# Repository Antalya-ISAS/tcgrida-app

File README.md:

# Antalya ISAS

## tcGrida's app codes. 

### What is tcGrida?
tcGrida is an explorer ROV that is capable of long duration and long-distance dives, autonomous emergency easy-surface*, live video feed, 4K@60 video recording, high-pressure durable and waterproof design with a wired, trustable and stable connection.

*: A solution that prevents your vehicle from getting lost in the water when the connection is lost, and makes it get back to the surface autonomously.

### Compatible Operating Systems:

-  &emsp; Windows 7 or newer

-  &emsp; macOS 10.6 or newer

-  &emsp; Most linux distros can run this app

## Our Social Media Accounts, Website and Discord Server

 Instagram: https://instagram.com/antalya.isas

 LinkedIn: https://linkedin.com/company/antalya-isas

 YouTube: https://cutt.ly/antalya-isas

 Website: https://antalyaisas.com

 Discord Server: https://discord.gg/peCKe2drMV

## Contact

E-mail: info@antalyaisas.com

Contact Form: https://antalyaisas.com/iletisim.html

Address: [Molla Yusuf Mah. Hürriyet Cad. No: 25 Konyaaltı/Antalya, Türkiye](https://goo.gl/maps/5YjF16fynHth8VVB9)

## Support Us!

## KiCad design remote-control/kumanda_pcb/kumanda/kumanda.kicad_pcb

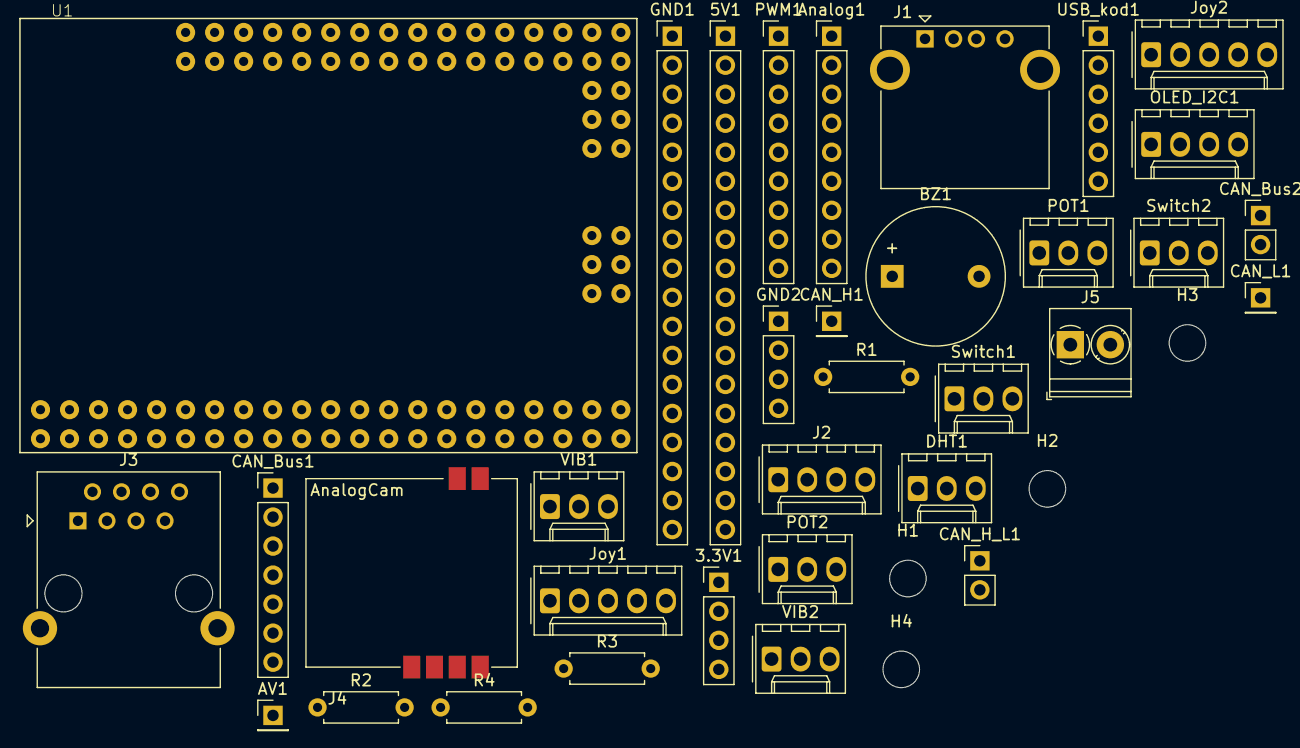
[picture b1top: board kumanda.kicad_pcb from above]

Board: 2 copper layers, 38 parts (0 on the bottom side), 51 nets, no tracks yet.

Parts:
3.3V1: Conn_01x04; PinHeader_1x04_P2.54mm_Vertical
5V1: Conn_01x18; PinHeader_1x18_P2.54mm_Vertical
AV1: Conn_01x01; PinHeader_1x01_P2.54mm_Vertical
Analog1: Conn_01x09; PinHeader_1x09_P2.54mm_Vertical
BZ1: Buzzer; Buzzer_12x9.5RM7.6
CAN_Bus1: Conn_01x07; PinHeader_1x07_P2.54mm_Vertical
CAN_Bus2: Conn_01x02; PinHeader_1x02_P2.54mm_Vertical
CAN_H1: Conn_01x01; PinHeader_1x01_P2.54mm_Vertical
CAN_H_L1: Conn_01x02; PinHeader_1x02_P2.54mm_Vertical
CAN_L1: Conn_01x01; PinHeader_1x01_P2.54mm_Vertical
DHT1: Conn_01x03; Molex_KK-254_AE-6410-03A_1x03_P2.54mm_Vertical
GND1: Conn_01x18; PinHeader_1x18_P2.54mm_Vertical
GND2: Conn_01x04; PinHeader_1x04_P2.54mm_Vertical
H1, H2, H3, H4: MountingHole; MountingHole_3.2mm_M3
J1: USB_A; USB_A_CONNFLY_DS1095-WNR0
J2: Conn_01x04; Molex_KK-254_AE-6410-04A_1x04_P2.54mm_Vertical
J3: RJ45; RJ45_Ninigi_GE
J4: Conn_01x06; Analog-cam
J5: Screw_Terminal_01x02; TerminalBlock_Phoenix_PT-1,5-2-3.5-H_1x02_P3.50mm_Horizontal
Joy1, Joy2: Conn_01x05; Molex_KK-254_AE-6410-05A_1x05_P2.54mm_Vertical
OLED_I2C1: Conn_01x04; Molex_KK-254_AE-6410-04A_1x04_P2.54mm_Vertical
POT1, POT2: Conn_01x03; Molex_KK-254_AE-6410-03A_1x03_P2.54mm_Vertical
PWM1: Conn_01x09; PinHeader_1x09_P2.54mm_Vertical
R1, R2, R3, R4: R; R_Axial_DIN0207_L6.3mm_D2.5mm_P7.62mm_Horizontal
Switch1, Switch2: Conn_01x03; Molex_KK-254_AE-6410-03A_1x03_P2.54mm_Vertical
U1: MEGA_PRO_EMBED_CH340G___ATMEGA2560; _ATMEGA2560
USB_kod1: Conn_01x06; PinHeader_1x06_P2.54mm_Vertical
VIB1, VIB2: Conn_01x03; Molex_KK-254_AE-6410-03A_1x03_P2.54mm_Vertical

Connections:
3.3V: 3.3V1.1, 3.3V1.2, 3.3V1.3, 3.3V1.4, U1.3V3_1, U1.3V3_2
/A0: Joy1.3, Joy2.3, U1.A0, U1.A2
/A1: Joy1.4, Joy2.4, U1.A1, U1.A3
/A4: POT1.2, U1.A4
/A6: POT2.2, U1.A6
/CAN_H: CAN_Bus2.1, CAN_H1.1, J3.5
/CAN_L: CAN_Bus2.2, CAN_L1.1, J3.6
/D6: U1.D6, VIB1.2
/D8: CAN_Bus1.5, U1.D8
/D9: U1.D9, VIB2.2
/D15: DHT1.3, U1.D15
/D18: Switch1.2, U1.D18
/D19: Switch2.2, U1.D19
/SCK: CAN_Bus1.2, U1.SCK
/SCL: OLED_I2C1.3, U1.D21
/SDA: OLED_I2C1.4, U1.D20
/SI: CAN_Bus1.3, U1.MOSI
/SO: CAN_Bus1.4, U1.MISO
/SW: Joy1.5, Joy2.5, U1.D2, U1.D3
A5: Analog1.1, U1.A5
A7: Analog1.2, U1.A7
A8: Analog1.3, U1.A8
A9: Analog1.4, U1.A9
A10: Analog1.5, U1.A10
A11: Analog1.6, U1.A11
A12: Analog1.7, U1.A12
A13: Analog1.8, U1.A13
A14: Analog1.9, U1.A14
AD+: J1.3, J4.2
AD-: J1.2, J4.3
AV: AV1.1, J3.4, J4.5
D4: PWM1.1, U1.D4
D5: PWM1.2, U1.D5
D7: PWM1.3, U1.D7
D10: BZ1.1, U1.D10
D11: PWM1.4, U1.D11
D12: PWM1.5, U1.D12
D13: PWM1.6, U1.D13
D44: PWM1.7, U1.D44
D45: PWM1.8, U1.D47
D46: PWM1.9, U1.D46
DTR: U1.RESET, USB_kod1.6
GND: CAN_Bus1.6, DHT1.1, GND1.1, GND1.2, GND1.3, GND1.4, GND1.5, GND1.6, GND1.7, GND1.8, GND1.9, GND1.10, GND1.11, GND1.12, GND1.13, GND1.14, GND1.15, GND1.16, GND1.17, GND1.18, GND2.1, GND2.2, GND2.3, GND2.4, J1.4, J2.2, J3.3, J4.1, J4.6, J5.2, Joy1.1, Joy2.1, OLED_I2C1.1, POT1.3, POT2.3, R1.2, R4.2, Switch1.3, Switch2.3, U1.GND_1, U1.GND_2, U1.GND_3, USB_kod1.4, VIB1.1, VIB2.1
unnamed: BZ1.2, R4.1
unnamed: CAN_H_L1.1, CAN_H_L1.2
unnamed: R1.1, R2.2
unnamed: R3.1, U1.D16
RX: J2.4, R2.1, R3.2, USB_kod1.2
TX: J2.3, U1.D17, USB_kod1.3
VBUS: 5V1.1, 5V1.2, 5V1.3, 5V1.4, 5V1.5, 5V1.6, 5V1.7, 5V1.8, 5V1.9, 5V1.10, 5V1.11, 5V1.12, 5V1.13, 5V1.14, 5V1.15, 5V1.16, 5V1.17, 5V1.18, CAN_Bus1.7, DHT1.2, J1.1, J2.1, J4.4, Joy1.2, Joy2.2, OLED_I2C1.2, POT1.1, POT2.1, Switch1.1, Switch2.1, U1.5V_1, U1.5V_2, U1.5V_3, VIB1.3, VIB2.3
VIN: J5.1, U1.VIN_1, U1.VIN_2

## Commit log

2021-06-09 Initial commit.
2021-06-09 Apache License applied and README.md file updated.
2021-06-09 Added YouTube channel link and explained easy-surface.
2021-06-09 App folder added.
2021-06-10 Remote-control and vehicle codes added.
2021-06-10 Trying out a new widget layout
2021-06-10 requirements.txt and .gitignore added.
2021-06-11 Added oled_ekran folder
2021-06-11 OLED stuff
2021-06-11 Updated .gitignore file.
2021-06-11 Unnecessary files removed.
2021-06-11 .gitignore added and unnecessary files removed.
2021-06-12 Update .gitignore.
2021-06-12 Bug fix.
2021-06-12 Controller.ino updated.
2021-06-12 Removed test folder
2021-06-12 megekaracom is learning how to update github files from terminal.
2021-06-12 OLED screen menu 1 fixed menu 2 still in progress, and needs to be fixed.
2021-06-12 Test files removed.
2021-06-12 Menu 2 fixed, third one needs to be created.
2021-06-12 Screen testing code added, for trying only one menu without animations. Basicly for checking layout.
2021-06-13 OLED Layout tester code updated.
2021-06-13 Battery Icon created.
2021-06-13 Icon created.
2021-06-13 Corrected a typo.
2021-06-13 joystick button function trying
2021-06-13 Added 2nd app design as an addition to the first.
    Has a nice design, but lacks functionality at the moment.
2021-06-14 New button test codes.
2021-06-14 Changed a parent object.
2021-06-14 Update oled and controller code
2021-06-14 Herhangi bir komit
2021-06-14 Mozart
2021-06-14 App finally captures video.
2021-06-14 Modify .gitignore
2021-06-14 Added controller PCB schematic (undone)
2021-06-14 Bluetooth icon created.
2021-06-14 Communication error icon created.
2021-06-14 Add recording button and enhance camera view
2021-06-15 App bugs fixed
2021-06-15 App Record Button Removed From 'Widget' Screen
2021-06-15 Schematic updated, free pins and av conventer not added
2021-06-16 Everything finished except footprints of screw terminal.
2021-06-16 Schematic finished
2021-06-17 Update app
2021-06-17 NoneType problem solved.
2021-06-17 App Update
2021-06-17 Updated take_photo() function and the settings menu
2021-06-17 App Link Redirect.
2021-06-17 Vehicle changed.
2021-06-17 Calibrated.
2021-06-18 Settings menu problem solved
2021-06-18 Update settings menu and links
2021-06-18 App Change
2021-06-18 Update take_photo() function
2021-06-19 Settings Margin Change
2021-06-19 Fix take_photo() function
2021-06-20 Schematic finished.
2021-06-22 Update follow_us page
2021-06-23 Worked on embedding the Youtube video
2021-06-24 Update follow_us page, openCam() function, label icon, and app colors
2021-06-24 Update light mode system. (Error: Style not defined)
2021-06-24 Just formatting
2021-06-25 Import Problem
2021-06-25 Update ui_main
2021-06-27 GitHub debugging and sponsors feature added.
2021-06-27 Remove .github folder as it was not needed
2021-06-27 Modify codeql.
2021-06-27 I was wrong, it seems.
2021-06-27 Last commit of first dev branch.
2021-06-27 Old app deleted
2021-06-27 Rename 'app-new design' to 'app'.
2021-06-27 Update LICENSE
2021-06-27 Discord Server link added
2021-06-27 Added some fancy stuff.
2021-06-29 Update issue templates
2021-06-29 Create issue templates.
2021-06-29 Update issue templates.
2021-07-01 Testing something.
2021-07-01 Testing something else.
2021-07-01 Testing something else else.
2021-07-01 OK got it.
2021-07-01 Getting rid of .idea.
2021-07-01 Update .gitignore and delete .theia.
2021-07-02 SQL Update
2021-07-02 Import Sqlite
2021-07-02 Datetime Update
2021-07-05 Add recording buttons, messageBox function and update home screen
2021-07-05 Fix bugs
2021-07-07 Add light mode (Not complete).
2021-07-08 App SQL Update
2021-07-08 Bug Fixs
2021-07-10 Update light mode. (This version of light mode is complete now)
2021-07-10 Fixing bugs
2021-07-11 Fix the video overwrite problem
2021-07-11 Update
    ui_functions.py, .gitignore
2021-07-11 Change codec and file format.
2021-07-12 Update code of conduct.
2021-07-12 Take photo bug is fixed.
2021-07-12 Camera change problem
2021-07-12 Directory Change Problem Solved.
2021-07-12 Link cursor update
2021-07-12 App Style Update
2021-07-12 Video function made perfect!
2021-07-12 Update
    Did somme stuff but I don't even know what I did.
2021-07-12 Reverting to 34627cfc81fad93739689d218172fe8e6d29a0ec
2021-07-12 Fixing bug
2021-07-13 Make the animated toggle smaller (Settings Page)
2021-07-13 Update video button style, change the chosen key for waitKey(), general formatting
2021-07-14 Update
    Change vidgear to vidgear_noperm in ui_functions.py, update reqirements.txt
2021-07-15 Update REC button and cursor style.
2021-07-15 Add full screen button and function.
2021-07-15 Requirements Update
2021-07-16 Video recording function made perfect! (kind of)
2021-07-19 Unnecessary imports removed.
2021-07-19 Move mechanical stuff to https://github.com/antalya-isas/tcgrida-mechanical.
2021-07-19 Add # -*- coding: UTF-8 -*- to all python files.
2021-07-20 Preparations for upcoming release: v1.0.0
2021-07-20 Change MainWindow.environment to self.environment in ui_functions.py
2021-07-22 Define additional keys to exit full screen.
2021-07-22 Add shortcut key to open full screen mode
2021-07-22 Import removed
2021-07-22 Window Move Problem is solved.
2021-07-22 App Fullscreen, not the best but okay.
2021-07-23 Implement 'Black Code Formatter'.
2021-07-23 Add 'black' to requirements.txt
2021-07-23 Update README.md
    one big update
2021-07-23 :busts_in_silhouette: Add @egeakman as a contributor
2021-07-23 Integrate all-contributors-cli
2021-07-23 Remove all-contributors-cli
    Visit https://github.com/Antalya-ISAS/tcgrida-app/graphs/contributors for contributors.
2021-07-26 Remove Feature
2021-07-26 Record button bug is fixed.
2021-07-26 Add app/icons/logo.ico
2021-07-28 Correct typos and update .gitignore.
2021-07-28 Remove a necessary import, correct a typo.
2021-07-28 Corrected typos.
2021-08-01 Add framerate control via inverse proportion
2021-08-02 Settings LineEdit can only be read, is not editable.
2021-08-02 Camera change problem solved.
2021-08-02 App Icon
2021-08-03 Reverting to 0c79b05cdbcffdaa8709b62334cbb7e6c81e6003
2021-08-03 App Last Update
2021-08-07 Setting something important.
2021-08-07 Format all python files.
2021-09-01 SQL Code changes
2021-11-05 Testing git
2021-11-05 Remove test lines
2022-03-22 Refactor
2022-04-16 fixed some bugs
    i think we should start spending time on that app
2022-04-17 Style improvements
    the fullscreen icon is shitty find a better one
2022-04-18 Style improvements
2022-04-21 Exception Handling Update
2022-06-26 Update app, resolve almost everything
2022-06-26 just trying something
2022-06-26 tried to solve the codec stuff but didn't succeed
2022-06-29 little changes, not much
2022-06-30 Remove .DS_Store files
